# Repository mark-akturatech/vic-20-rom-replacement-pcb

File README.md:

# Commodore VIC20 ROM Replacement Project

## Description

My VIC20's Basic ROM is kaput. So took the opportunity to design a simple PCB to allow both the basic ROM and the Kernal (this is how Commodore spell Kernel) ROM to be replaced with a single 27C256 (this is what I had - double what is needed).

## Development

The project is constructed in Kicad. The output files are generated in Gerber format.

## Design

The PCB replaces the Basic ROM and Kernal ROM. The PCB plugs in to the Basic ROM socket and also runs a single fly lead to Pin 20 of the Kernal ROM socket (with Kernal ROM completely removed).

A quad AND gate is used to control the output enable line of the EPROM and is also used to enable the additional banks on the EPROM when switched.

As the EPROM is twice the required size, this allows us to include two Basic ROMs and two Kernal ROMs in the EPROM. Address line 13 can then be switched to enable the second ROM.

Contacts are provided for two switches. The first switch switches Basic ROM between bank 1 and bank 2 and the second switches the Kernal ROM between bank 1 and 2.

The circuit simply achieves the following:

1. Connects the appropriate pins from the Basic ROM to the EPROM to achieve like for like.
2. Enables chip output if either the Basic or Kernal ROM is chip enabled. This is achieved using a single AND gate with BASIC ROM and Kernal ROM chip enable pins (high if not enabled) connected to the inputs.
3. Sets address line 14 high if the Basic ROM is not chip enabled (therefore allowing the Kernal ROM to be included in the top 16k of the EPROM).
4. Sets address line 13 high if the appropriate switch is selected. This is achieved using 2 AND gates. The first takes the input of switch 1 (high when switched) and the chip enable of the Kernal ROM. If the Kernal ROM C/E is high we assume the Basic ROM is enabled instead and therefore if the switch is high, we switch in address line 13 (14 should be low at this point). Note that it is possible for neither the Kernal or Basic ROM to be enabled and in this case the AND gate will incorrectly assume the Basic ROM is enabled however this is fine as in this case the EPROM output enable will be disabled (see item 2). The second AND gate takes the Basic ROM chip enable and Switch 2 (high on active) inputs. The output will enable if Kernal ROM is active and the switch is set. The output of both AND gates are joined and connected to address line 13.

## EPROM Configuration

The EPROM is segmented as follows:

- 0k-8k Basic ROM (bank 1) Address line 13 LOW; Address line 14 LOW
- 8k-16k Basic ROM (bank 2) Address line 13 HIGH; Address line 14 LOW
- 16k-24k Kernal ROM (bank 1) Address line 13 LOW; Address line 14 HIGH
- 24k-32k Kernal ROM (bank 2) Address line 13 HIGH; Address line 14 HIGH

The ROM configuration I have used is as follows:

- 0k-8k basic.901486-01
- 8k-16k basic.901486-01 (duplicated)
- 16k-24k kernal.901486-07
- 24k-32k JiffyDOS_VIC-20

A switch is connected between +5v and switch 2. Switch 1 is left disconnected.

## Part List & Build Instructions

2 x 20 contact (only need 12 contact by 20 is more common) Board-to-Board through hole straight pin headers.
For example <https://au.element14.com/amp-te-connectivity/2-826629-0/btb-conn-header-20pos-1row-2-54mm/dp/1580047>
These are soldered to the 2 rows of 12 through-holes on the underside of the board and are used to plug in to the Basic ROM socket.
Solder these first.

1 x 28 contact DIP 2.5mm x 15.24mm socket. The socket should slightly stand off the board to not interfere with the pin headers.
For example <https://au.element14.com/multicomp/2227mc-28-06-07-f1/socket-ic-dil-0-6-28way/dp/1103852>
This soldered to the topside of the PCB for mounting the 27C256.

1 x SN74LS08n quad AND gate.
For example <https://au.element14.com/texas-instruments/sn74ls08n/logic-quad-2-inputgate-14dip/dp/3120526>

2 x optional single pole miniature toggle switches (only single throw required)
For example <https://au.element14.com/e-switch/100sp1t1b1m1qeh/toggle-switch-spdt-5a-120vac-28vdc/dp/2522278>
The switches are wired to B2 En (basic bank 2 enable) and K2 En (Kernal bank 2 enable)

1 x 10cm of wire to connext "Kernal Pin 20" contact to pin 20 of the Kernal ROM.
Tin the end of the wire so it fits firmly into the socket.

1 x 27C256 EPROM (or compatible - eg AT28C256 will also work)
I've used a write once compatible EPROM here.

## Optional Switches

Each switch is wired as follows:

- Center pin to EN, top pin to GND, bottom pin to +5V.

Note that the EN should be tied to GND on the PCB if the switch is not used.

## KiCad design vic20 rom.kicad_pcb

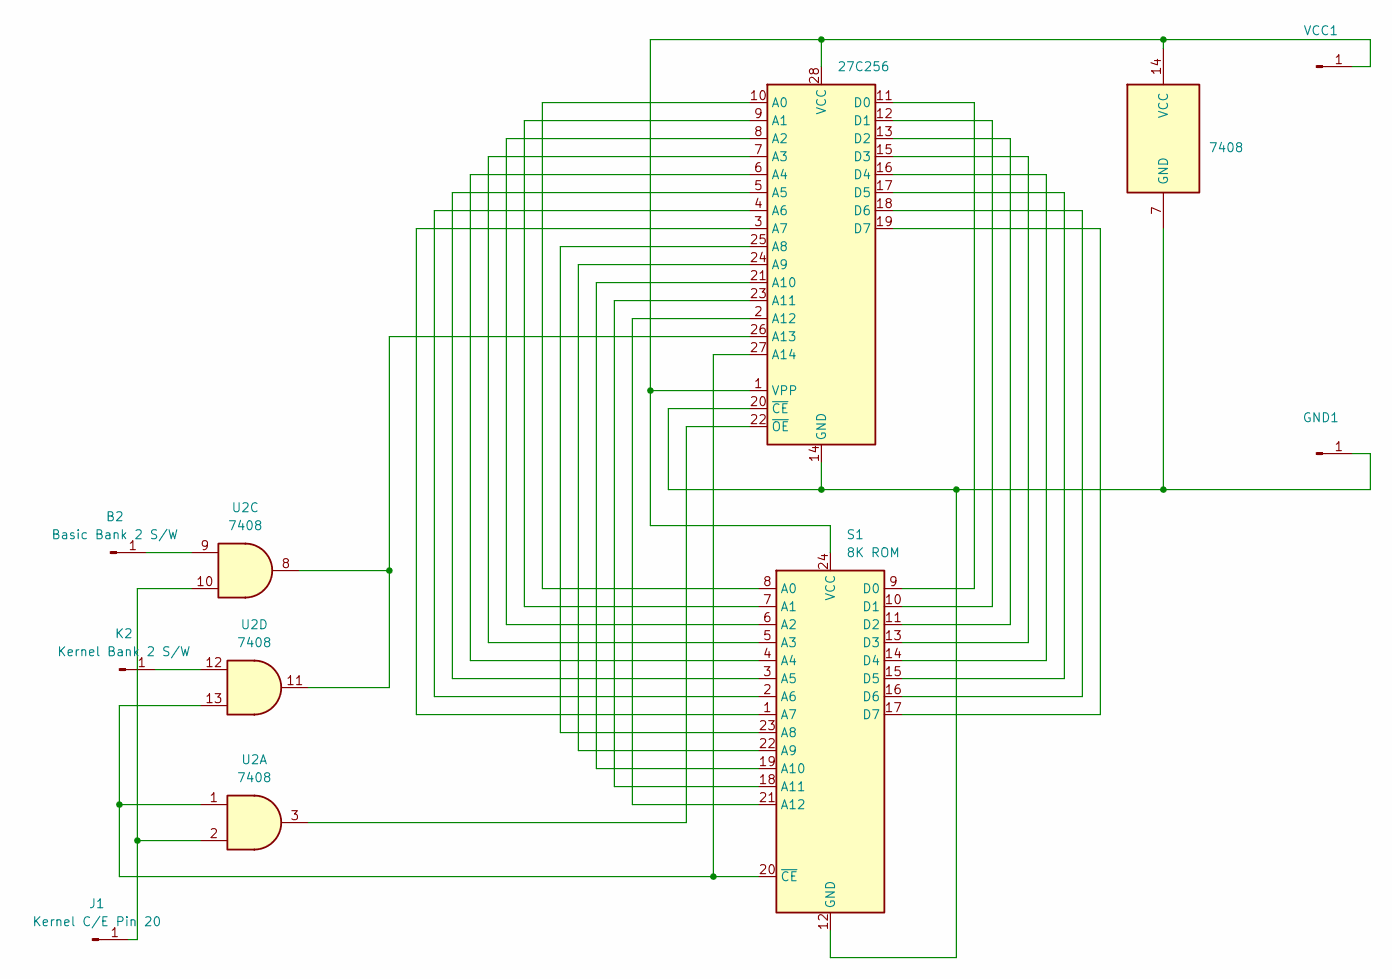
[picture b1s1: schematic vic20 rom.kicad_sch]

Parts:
B2: Basic Bank 2 S/W; Pin_D0.7mm_L6.5mm_W1.8mm_FlatFork
GND1: GND; Pin_D0.7mm_L6.5mm_W1.8mm_FlatFork
J1: Kernel C/E Pin 20; Pin_D0.7mm_L6.5mm_W1.8mm_FlatFork
K2: Kernel Bank 2 S/W; Pin_D0.7mm_L6.5mm_W1.8mm_FlatFork
S1: 8K ROM; DIP-24_W15.24mm
U1: 27C256; DIP-28_W15.24mm
U2: 7408; DIP-14_W7.62mm
VCC1: +5V; Pin_D0.7mm_L6.5mm_W1.8mm_FlatFork

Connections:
unnamed: B2.1, U2.9
unnamed: GND1.1, S1.12 (GND), U1.14 (GND), U1.20 (~CE), U2.7 (GND)
unnamed: J1.1, U2.2, U2.10
unnamed: K2.1, U2.12
unnamed: S1.8 (A0), U1.10 (A0)
unnamed: S1.7 (A1), U1.9 (A1)
unnamed: S1.6 (A2), U1.8 (A2)
unnamed: S1.5 (A3), U1.7 (A3)
unnamed: S1.4 (A4), U1.6 (A4)
unnamed: S1.3 (A5), U1.5 (A5)
unnamed: S1.2 (A6), U1.4 (A6)
unnamed: S1.1 (A7), U1.3 (A7)
unnamed: S1.23 (A8), U1.25 (A8)
unnamed: S1.22 (A9), U1.24 (A9)
unnamed: S1.19 (A10), U1.21 (A10)
unnamed: S1.18 (A11), U1.23 (A11)
unnamed: S1.21 (A12), U1.2 (A12)
unnamed: S1.9 (D0), U1.11 (D0)
unnamed: S1.10 (D1), U1.12 (D1)
unnamed: S1.11 (D2), U1.13 (D2)
unnamed: S1.13 (D3), U1.15 (D3)
unnamed: S1.14 (D4), U1.16 (D4)
unnamed: S1.15 (D5), U1.17 (D5)
unnamed: S1.16 (D6), U1.18 (D6)
unnamed: S1.17 (D7), U1.19 (D7)
unnamed: S1.24 (VCC), U1.1 (VPP), U1.28 (VCC), U2.14 (VCC), VCC1.1
unnamed: S1.20 (~CE), U1.27 (A14), U2.1, U2.13
unnamed: U1.26 (A13), U2.8, U2.11
unnamed: U1.22 (~OE), U2.3

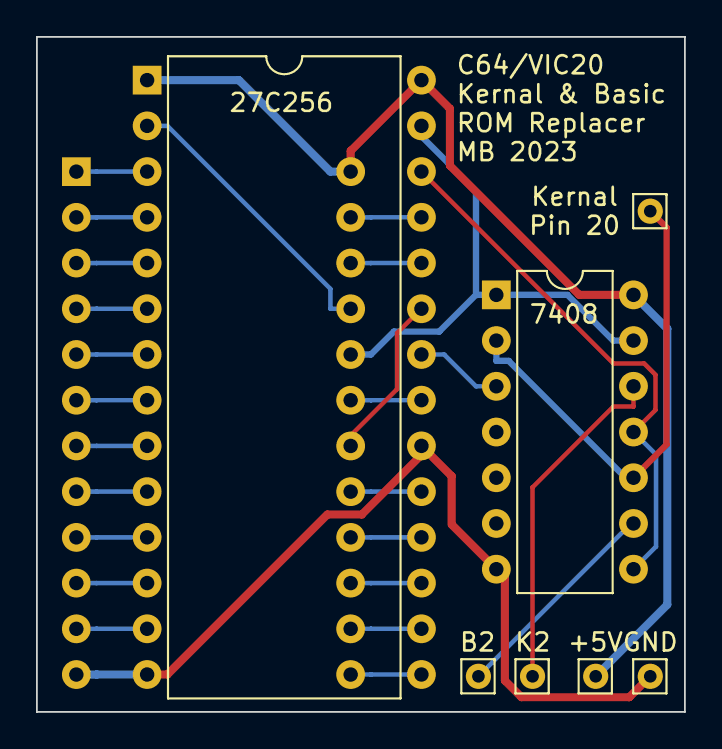
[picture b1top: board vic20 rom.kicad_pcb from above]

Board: 2 copper layers, 36.0 x 37.5 mm, 8 parts (0 on the bottom side), 29 nets.

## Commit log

2023-08-02 Master: Initial commit
2023-08-02 Master: Added GND pin for switches
2023-08-02 Master: Added PCB images to readme file
